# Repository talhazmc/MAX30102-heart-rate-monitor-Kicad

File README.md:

# MAX30102 Heart Rate and SpO2 Monitor PCB Design

This repository contains my KiCad PCB design project for a MAX30102-based heart rate and SpO2 monitoring system.

The project was designed as a compact embedded system board using an Arduino Nano, MAX30102 pulse oximeter sensor, SSD1306 OLED display, user buttons, and alarm indicator components.

---

## Project Overview

The main purpose of this project was to design a PCB for a basic biomedical signal monitoring application.

The system uses the MAX30102 sensor module to detect pulse-related optical signals. An Arduino Nano processes the sensor data and displays the measured values on an SSD1306 OLED screen.

The board also includes buttons for user interaction and an alarm LED section for visual warning or status indication.

---

## 3D PCB View

The 3D view shows the physical placement of the main components, including the Arduino Nano, MAX30102 sensor module, SSD1306 OLED display, buttons, resistors, capacitors, and alarm LED.

---

## PCB Layout

The PCB layout was created in KiCad.  
The board includes separated sections for the sensor module, OLED display, Arduino Nano, control buttons, and alarm indicator.

---

## Main Components

- Arduino Nano
- MAX30102 heart rate and SpO2 sensor module
- SSD1306 OLED display
- Push buttons
- Alarm LED
- Resistors
- Capacitors
- I2C communication lines
- Mounting holes

---

## Working Principle

The MAX30102 sensor works by using red and infrared light to measure changes in blood flow. These optical signals can be used to estimate heart rate and blood oxygen saturation.

The Arduino Nano communicates with the MAX30102 sensor over I2C. It reads the sensor data, processes the measurements, and sends the results to the SSD1306 OLED display.

The push buttons can be used for menu control, navigation, or user input. The alarm LED can be used as a warning indicator when a defined threshold or condition is detected.

---

## PCB Design Notes

- The MAX30102 and SSD1306 modules use I2C communication.
- Arduino Nano was placed near the center for easy routing.
- Buttons were placed on the right side for user interaction.
- The alarm LED was placed at the top-right side for visibility.
- Mounting holes were added for mechanical fixing.
- The board was checked using KiCad 3D Viewer.

---

## What I Learned

Through this project, I gained practical experience in:

- Designing sensor-based embedded system PCBs
- Using KiCad for PCB layout and 3D visualization
- Working with I2C-based modules
- Integrating MAX30102 and SSD1306 modules
- Designing user interface buttons on PCB
- Creating a compact health-monitoring prototype board
- Organizing PCB sections for readability and functionality

---

## Tools and Technologies

- KiCad
- Arduino Nano
- MAX30102
- SSD1306 OLED Display
- I2C Communication
- PCB Design
- Embedded Systems
- Biomedical Sensor Applications

---

## Note

This project is an educational prototype and is not intended to be used as a medical device.

---

## Author

**Talha Üzümcü**  
Electrical and Electronics Engineer  
GitHub: [talhazmc](https://github.com/talhazmc)

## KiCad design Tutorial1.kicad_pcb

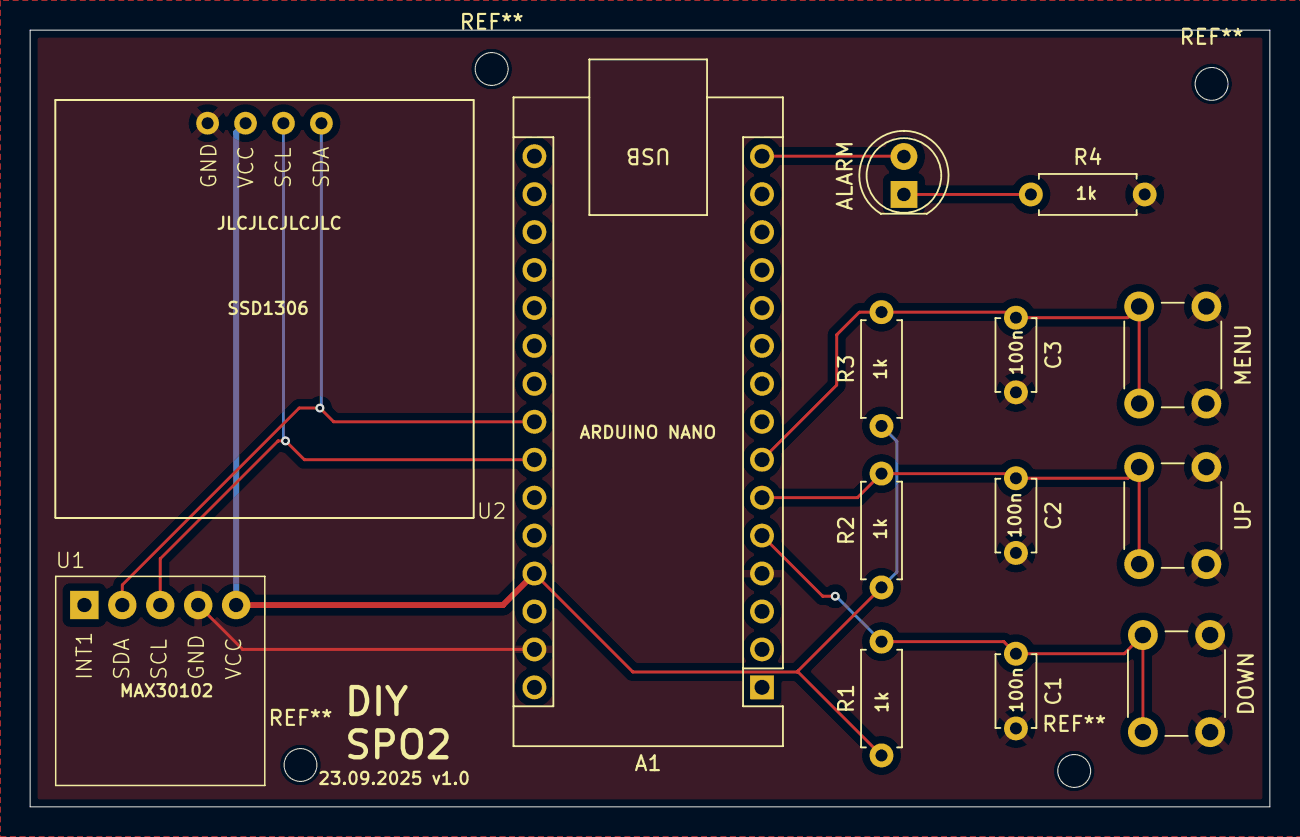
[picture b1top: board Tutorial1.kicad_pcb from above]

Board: 4 copper layers, 83.0 x 52.0 mm, 14 parts (0 on the bottom side), 9 nets.

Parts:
A1: Arduino_Nano_v3.x; Arduino_Nano
ALARM: LED; LED_D5.0mm
C1, C2, C3: 100n; C_Disc_D4.7mm_W2.5mm_P5.00mm
DOWN: SW_Push; SW_PUSH_6mm
MENU: SW_Push; SW_PUSH_6mm
R1, R2, R3, R4: 1k; R_Axial_DIN0207_L6.3mm_D2.5mm_P7.62mm_Horizontal
U1: MAX30102
U2: SSD1308
UP: SW_Push; SW_PUSH_6mm

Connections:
+5V: A1.27 (+5V), R1.1, R2.1, R3.1, U1.5 (VCC), U2.5 (VCC)
GND: A1.4 (GND), A1.29 (GND), C1.2, C2.2, C3.2, DOWN.1, MENU.1, R4.2, U1.4 (GND), U2.4 (GND), UP.1
unnamed: A1.23 (A4), U1.2 (SDA), U2.2 (SDA)
unnamed: A1.24 (A5), U1.3 (SCL), U2.3 (SCL)
unnamed: A1.5 (D2), C1.1, DOWN.2, R1.2
unnamed: A1.6 (D3), C2.1, R2.2, UP.2
unnamed: A1.7 (D4), C3.1, MENU.2, R3.2
unnamed: A1.15 (D12), ALARM.2 (A)
unnamed: ALARM.1 (K), R4.1

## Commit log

2026-06-24 images
2026-06-24 Add README for MAX30102 heart rate monitor project
    This README provides an overview of the MAX30102 heart rate and SpO2 monitor PCB design project, including components, working principles, design notes, and tools used.
